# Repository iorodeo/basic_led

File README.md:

# IO Rodeo basic_led 

Hardware files for IO Rodeo's basic_led designed to be used with our
[cuvette holder](https://github.com/iorodeo/cuvette_holder).

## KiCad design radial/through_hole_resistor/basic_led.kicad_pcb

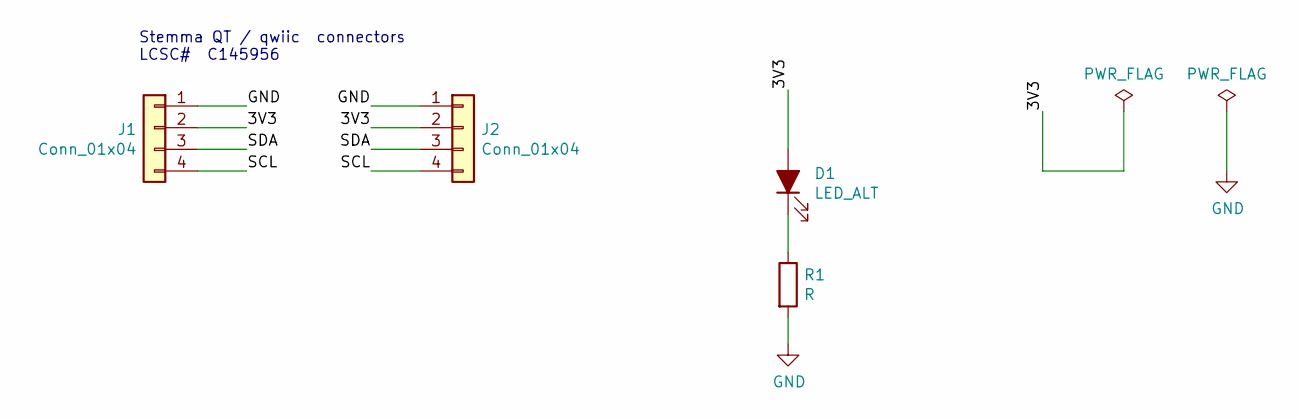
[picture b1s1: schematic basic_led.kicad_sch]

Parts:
D1: LED_ALT; LED_D3.0mm
J1, J2: Conn_01x04; BOOMELE_SMD_SH_4PIN_RT
R1: R; R_Axial_DIN0207_L6.3mm_D2.5mm_P7.62mm_Horizontal

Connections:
/3V3: D1.2 (A), J1.2, J2.2
/SCL: J1.4, J2.4
/SDA: J1.3, J2.3
GND: J1.1, J2.1, R1.2
unnamed: D1.1 (K), R1.1

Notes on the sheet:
Stemma QT / qwiic connectors LCSC# C145956

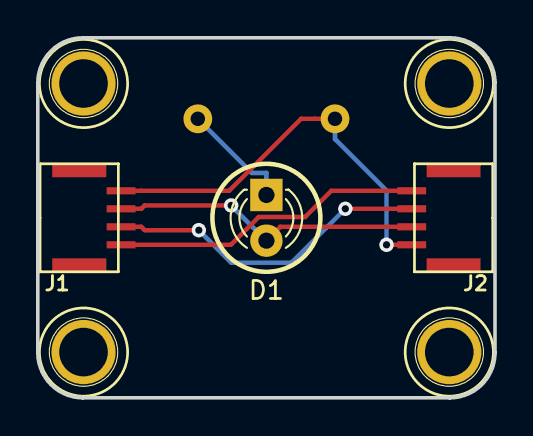
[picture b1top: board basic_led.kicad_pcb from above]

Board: 2 copper layers, 25.4 x 20.0 mm, 8 parts (1 on the bottom side), 5 nets.

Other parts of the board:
M1, M2, M3, M4: MountingHole_2.5mm_Pad

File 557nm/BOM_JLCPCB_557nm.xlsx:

Comment | Designator | Footprint | LCSC Part #（optional） | Qty
4-Pin Connector (BOOMELE) | J1 ,J2 | SMD,P=1mm | C145956 | 2
Resistor, 51 Ohm, 1% | R1 | 0603 | C2907050 | 1
LED (557nm) | D1 | 0603 | Global Parts | 1

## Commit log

2022-01-03 Project creation.
2022-10-11 Changed wavelength text on red LED from 625 to 630.
2022-10-11 Move 625nm subdirectory to 630nm subdirectory.
2022-10-11 Added 570nm led board. Renamed BOM & CPL for 630nm.
2022-10-12 Added 595mm led variant.
2022-10-13 Set resistors in BOM for 570 and 595 led boards.
2022-10-21 Adjusted orientations of connectors in CPL file.
2023-06-06 Added alternative BOM for 570 board.
2023-09-01 Added new designs.
2023-09-05 Added 496nm and 557nm LEDs.
2023-09-07 Added designs for radial through hole resistors, rearranged a bit.
2023-09-11 minor change
2023-09-11 Fixed typo in README
2023-09-17 Added LCSC number for 557nm and 496nm 3V3 0603 designs.
2023-09-17 Fixed issue in BOM of 557nm led.
